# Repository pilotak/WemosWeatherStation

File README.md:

# Wemos weather station

An all-in-one ESP8266 based weather station. Hardware configuration is split into two parts due to easier maintenance in case of ESP8266 failure and fuse replacement (the board outside is protected against lighting). FW can easily be compiled by PlatformIO or Arduino IDE if necessary, otherwise can be downloaded in **Releases**.

Data are sent over MQTT where [Telegraf](https://www.influxdata.com/time-series-platform/telegraf/) is waiting to push data to [InfluxDB](https://www.influxdata.com/time-series-platform/influxdb/) and [Grafana](https://grafana.com/) tool to render charts.

**Main futures:**
- Easy configuration via [WiFiManager](https://github.com/tzapu/WiFiManager)
- WeMos based shield
- WH1080 mechanical components for rain, wind measurements and radiation shield
- MCP9808: high precision temperature sensor
- HTU21D or SHT31D: humidity sensor
- BMP280 or LPS35HW: pressure sensor
- Output data is via MQTT
- supports Arduino OTA, HTTP OTA and [NoFuss OTA](https://github.com/xoseperez/espurna)

*Note: on the board there can be only one humidity sensor, one pressure sensor and one temperature sensor in any combination, please see `platformio.ini`*

## Wemos-meteo shield
Based on my libraries:
- [WeatherMeters](https://github.com/pilotak/WeatherMeters)
- [MeteoFunctions](https://github.com/pilotak/MeteoFunctions)

### MQTT topics:
#### `name/status`
If online:
`sensors` key: binary map of sensors state (OK=1, failure=0)
```json
{
  "status": 1,
  "ip": "192.168.1.7",
  "rssi": -10,
  "sensors": 7,
  "fw_ver": "1.0.0"
}
```

otherwise:
```json
{
  "status": 0
}
```

#### `name/sensors`
If any of the value can't be calculated, it sends `NaN`
```json
{
  "humidity_rel": 79.84,
  "humidity_abs": 14.93,
  "pressure_rel": 1021.85,
  "pressure_abs": 967.55,
  "dew": 2.13,
  "humidex": 3.69,
  "heat": 3.97,
  "cloud": 390.13,
  "temp": [
    5.32,
    5.36,
    5.43
  ]
}
```

#### `name/upgrade`
As a data send link to `*.bin` upgrade package and it will reply in topic `name/upgrade/status`
(HTTP support only) *ie.: `http://somewebsite.com/upload/package.bin`*

#### `name/height`
As a data send new height and it will confirm in topic `name/height/new`

<table border="0">
 <tr>
    <td></td>
    <td></td>
 </tr>
</table>

## Weather board
Fits directly into radiation shield, just connect wind sensors, rain gauge bucket and you ready to measure. For future i have included extention connector for measuring sun light and UV index.

**_Update, I have created a sencond version of WeatherBoard with water-proof sensors SHT31D and LPS35HW but be carefull they are difficult to solder due to its size._**

<table border="0">
 <tr>
    <td></td>
    <td></td>
    <td></td>
 </tr>
 <tr>
    <td></td>
    <td></td>
    <td></td>
 </tr>
</table>

## Server configuration
Below you can find a `docker-compose.yaml` file for fast integration onto your server.
```yaml
version: "3.6"

services:
  mosquitto:
    container_name: mosquitto
    restart: always
    image: eclipse-mosquitto
    ports:
      - 1883:1883
    volumes:
      - ${DOCKER_PATH}/mosquitto/mosquitto.conf:/mosquitto/config/mosquitto.conf
      - ${DOCKER_PATH}/mosquitto/pwfile:/mosquitto/config/pwfile
      - ${DOCKER_PATH}/mosquitto/data:/mosquitto/data

  influxdb:
    container_name: influxdb
    restart: always
    image: influxdb:alpine
    environment:
      - INFLUXDB_REPORTING_DISABLED=true
      - INFLUXDB_DB=${INFLUX_DB}
      - INFLUXDB_ADMIN_USER=${INFLUX_ADMIN_USER}
      - INFLUXDB_ADMIN_PASSWORD=${INFLUX_ADMIN_PASSWORD}
      - INFLUXDB_USER=${INFLUX_USER}
      - INFLUXDB_USER_PASSWORD=${INFLUX_PASSWORD}
      - INFLUXDB_READ_USER=${INFLUX_READ_USER}
      - INFLUXDB_READ_USER_PASSWORD=${INFLUX_READ_PASSWORD}
      - INFLUXDB_WRITE_USER=${INFLUX_WRITE_USER}
      - INFLUXDB_WRITE_USER_PASSWORD=${INFLUX_WRITE_PASSWORD}
      - INFLUXDB_HTTP_AUTH_ENABLED=true
    volumes:
      - ${DOCKER_PATH}/influxdb:/var/lib/influxdb
    ports:
      - 8086:8086

  grafana:
    container_name: grafana
    restart: always
    image: grafana/grafana
    depends_on:
      - influxdb
    environment:
      - GF_ANALYTICS_REPORTING_ENABLED=false
      - GF_ANALYTICS_CHECK_FOR_UPDATES=false
      - GF_SECURITY_DISABLE_GRAVATAR=true
      - GF_SNAPSHOTS_EXTERNAL_ENABLED=false
      - GF_AUTH_ANONYMOUS_ENABLED=true
      - GF_AUTH_ANONYMOUS_ORG_NAME=${INFLUX_DB}
      - GF_AUTH_ANONYMOUS_ORG_ROLE=Viewer
      - GF_AUTH_DISABLE_SIGNOUT_MENU=true
      - GF_AUTH_BASIC_ENABLED=false
      - GF_SERVER_ROOT_URL=https://meteo.${MY_DOMAIN}
    volumes:
      - ${DOCKER_PATH}/grafana:/var/lib/grafana
    ports:
      - 3000:3000

  telegraf_meteo:
    container_name: telegraf_meteo
    restart: always
    image: telegraf:alpine
    depends_on:
      - influxdb
      - mosquitto
    volumes:
      - ${DOCKER_PATH}/telegraf/meteo.conf:/etc/telegraf/telegraf.conf:ro

```

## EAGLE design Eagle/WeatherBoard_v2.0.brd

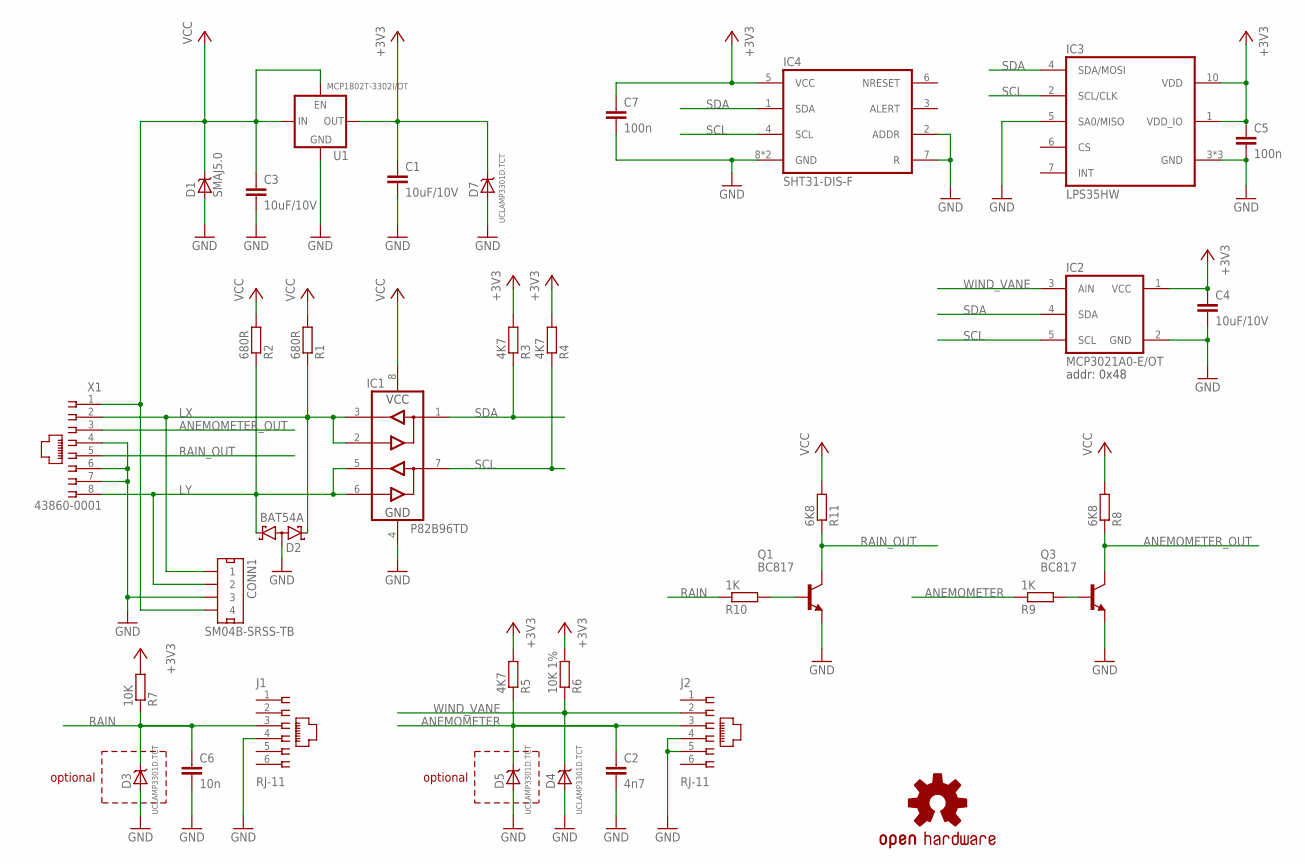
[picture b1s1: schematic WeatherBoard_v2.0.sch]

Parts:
C1, C3, C4: 10uF/10V; C0805
C2: 4n7; C0805
C5, C7: 100n; C0805
C6: 10n; C0805
CONN1: SM04B-SRSS-TB; JST-SRSS-4-T
D1: SMAJ5.0; DO214AC
D2: BAT54A; SOT23
D3, D4, D5, D7: UCLAMP3301D.TCT; SOD323
IC1: P82B96TD; SO08
IC2: MCP3021A0-E/OT; SOT23-5
IC3: LPS35HW; CCLGA10L
IC4: SHT31-DIS-F; DFN8
J1, J2: RJ-11; 615006138421
LOGO1: OSHW-LOGOM-COPPER; OSHW-LOGO-M_COPPER
Q1, Q3: BC817; SOT23-BEC
R1, R2: 680R; R0805
R3, R4, R5: 4K7; R0805
R6: 10K 1%; R0805
R7: 10K; R0805
R8, R11: 6K8; R0805
R9, R10: 1K; R0805
U1: MCP1802T-3302I/OT; SOT23-5
X1: 43860-0001; MX-43860-0001

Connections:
+3V3: C1.1, C4.1, C5.1, C7.1, D7.C, IC2.1 (VCC), IC3.1 (VDD_IO), IC3.10 (VDD), IC4.5 (VCC), R3.2, R4.2, R5.2, R6.2, R7.2, U1.5 (VOUT)
ANEMOMETER: C2.1, D5.C, J2.3, R5.1, R9.1
ANEMOMETER_OUT: Q3.C, R8.1, X1.3
GND: C1.2, C2.2, C3.2, C4.2, C5.2, C6.2, C7.2, CONN1.3, D1.A, D2.3 (AA), D3.A, D4.A, D5.A, D7.A, IC1.4 (GND), IC2.2 (GND), IC3.3 (GND), IC3.5 (SA0/MISO), IC3.8 (GND), IC3.9 (GND), IC4.2 (ADDR), IC4.7 (R), IC4.8 (GND), IC4.PAD (GND), J1.4, J2.4, J2.5, Q1.E, Q3.E, U1.2 (GND), X1.4, X1.6, X1.7
LX: CONN1.1, D2.2 (K2), IC1.2 (RX), IC1.3 (TX), R1.1, X1.2
LY: CONN1.2, D2.1 (K1), IC1.5 (TY), IC1.6 (RY), R2.1, X1.8
unnamed: Q3.B, R9.2
unnamed: Q1.B, R10.2
RAIN: C6.1, D3.C, J1.3, R7.1, R10.1
RAIN_OUT: Q1.C, R11.1, X1.5
SCL: IC1.7 (SY), IC2.5 (SCL), IC3.2 (SCL/CLK), IC4.4 (SCL), R4.1
SDA: IC1.1 (SX), IC2.4 (SDA), IC3.4 (SDA/MOSI), IC4.1 (SDA), R3.1
VCC: C3.1, CONN1.4, D1.C, IC1.8 (VCC), R1.2, R2.2, R8.2, R11.2, U1.1 (VIN), U1.3 (EN), X1.1
WIND_VANE: D4.C, IC2.3 (AIN), J2.2, R6.1

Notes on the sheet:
addr: 0x48
optional

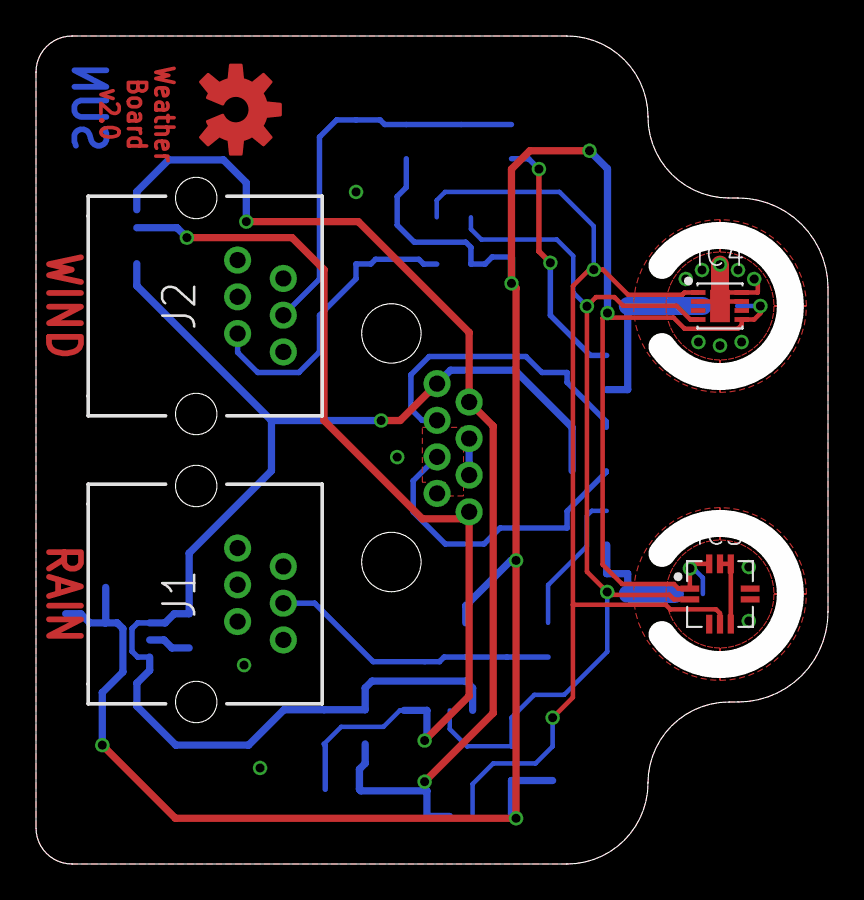
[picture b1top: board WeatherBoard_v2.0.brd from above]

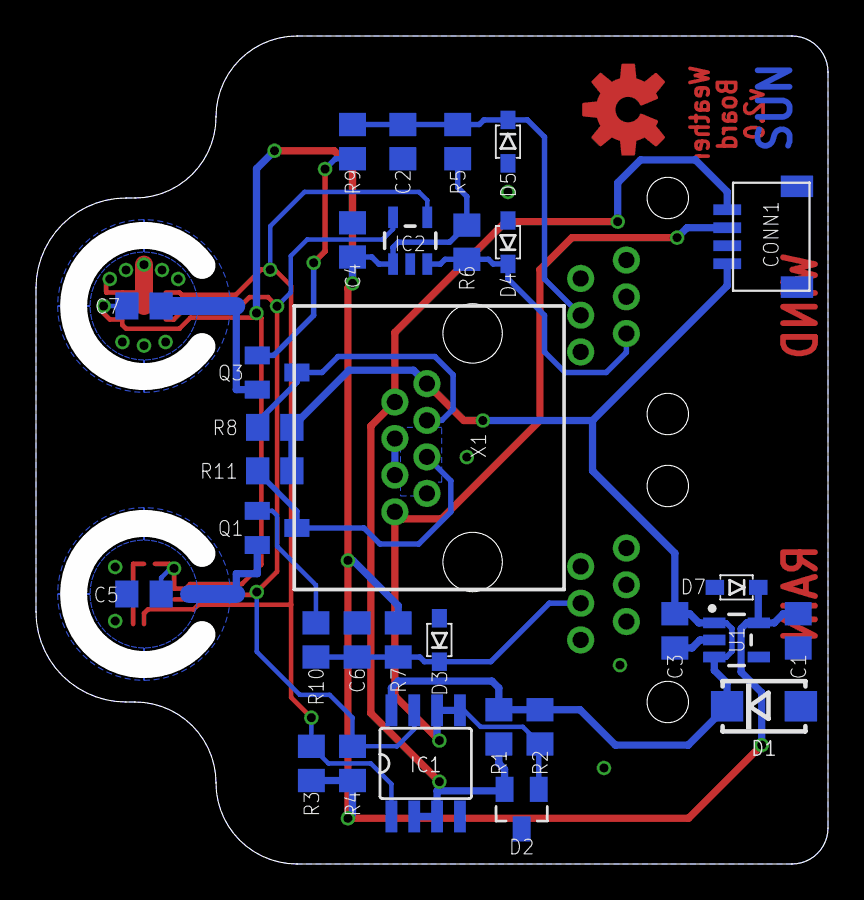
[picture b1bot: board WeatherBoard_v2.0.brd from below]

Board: 2 copper layers, 44.0 x 46.0 mm, 36 parts (31 on the bottom side), 14 nets.

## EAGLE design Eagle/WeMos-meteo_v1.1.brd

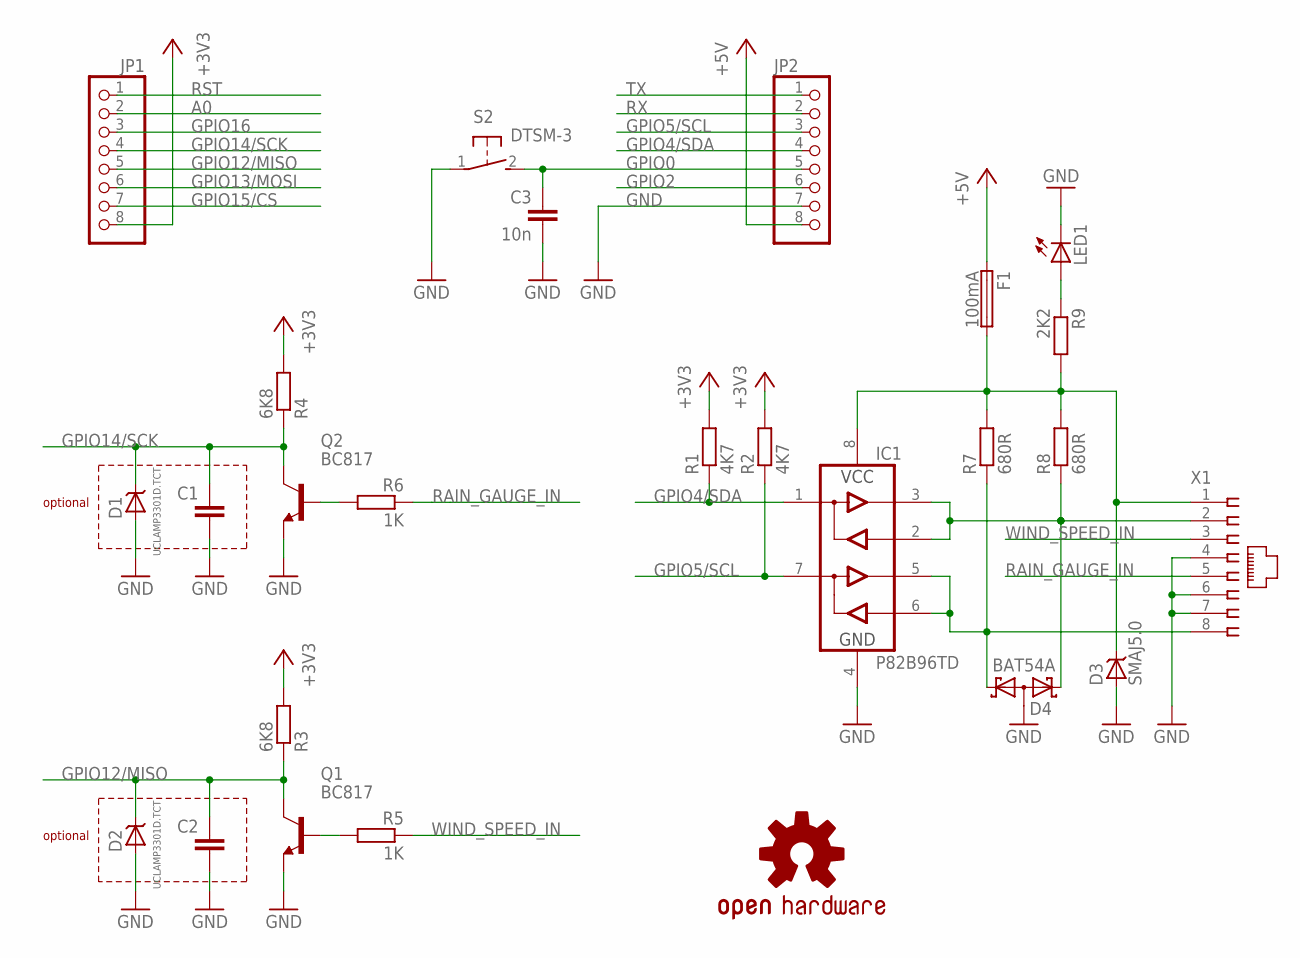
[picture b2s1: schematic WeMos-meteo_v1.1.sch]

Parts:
C1, C2: C-EUC0805; C0805
C3: 10n; C0805
D1, D2: UCLAMP3301D.TCT; SOD323
D3: SMAJ5.0; DO214AC
D4: BAT54A; SOT23
F1: 100mA; 19560
IC1: P82B96TD; SO08
JP1, JP2: PINHD-1X08_2.54-S; 1X08-S
LED1: LED0805
LOGO1: OSHW-LOGOMINI; OSHW-LOGO-MINI
Q1, Q2: BC817; SOT23-BEC
R1, R2: 4K7; R0805
R3, R4: 6K8; R0805
R5, R6: 1K; R0805
R7, R8: 680R; R0805
R9: 2K2; R0805
S2: DTSM-3
X1: RJ-45; 95501

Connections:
+3V3: JP1.8, R1.2, R2.2, R3.2, R4.2
+5V: F1.1, JP2.8
A0: JP1.2
GND: C1.2, C2.2, C3.2, D1.A, D2.A, D3.A, D4.3 (AA), IC1.4 (GND), JP2.7, LED1.C, Q1.E, Q2.E, S2.1, X1.4, X1.6, X1.7
GPIO0: C3.1, JP2.5, S2.2
GPIO2: JP2.6
GPIO4/SDA: IC1.1 (SX), JP2.4, R1.1
GPIO5/SCL: IC1.7 (SY), JP2.3, R2.1
GPIO12/MISO: C2.1, D2.C, JP1.5, Q1.C, R3.1
GPIO13/MOSI: JP1.6
GPIO14/SCK: C1.1, D1.C, JP1.4, Q2.C, R4.1
GPIO15/CS: JP1.7
GPIO16: JP1.3
unnamed: D4.2 (K2), IC1.2 (RX), IC1.3 (TX), R8.1, X1.2
unnamed: D4.1 (K1), IC1.5 (TY), IC1.6 (RY), R7.1, X1.8
unnamed: Q1.B, R5.2
unnamed: Q2.B, R6.2
unnamed: LED1.A, R9.1
RAIN_GAUGE_IN: R6.1, X1.5
RST: JP1.1
RX: JP2.2
TX: JP2.1
VCC: D3.C, F1.2, IC1.8 (VCC), R7.2, R8.2, R9.2, X1.1
WIND_SPEED_IN: R5.1, X1.3

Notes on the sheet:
optional

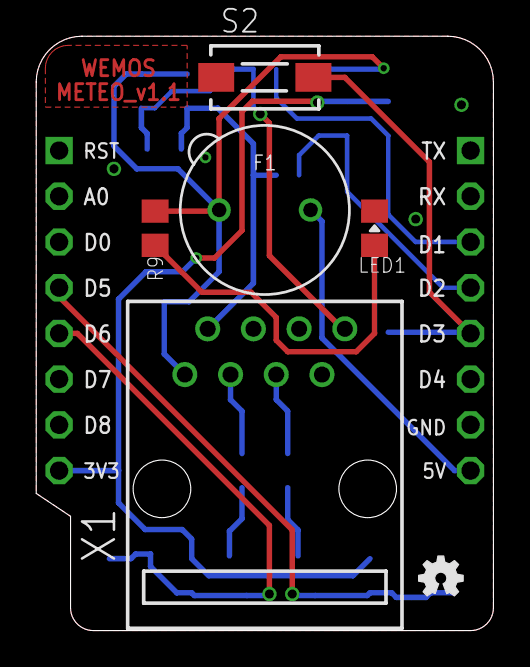
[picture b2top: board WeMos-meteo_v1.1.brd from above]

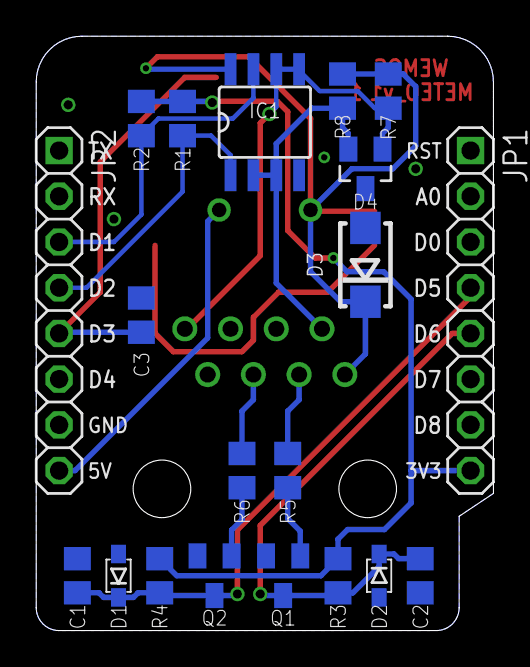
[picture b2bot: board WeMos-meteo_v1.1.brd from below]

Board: 2 copper layers, 25.4 x 33.0 mm, 26 parts (20 on the bottom side), 16 nets.

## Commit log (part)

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2018-09-15 init
2018-09-25 badge
2018-09-27 meteo functions added
2018-09-27 interrupt stop on OTA + enable timer WM
2018-10-14 mqtt IP check
2018-10-14 BME address fix
2018-10-17 check if sensors are available
2018-10-17 check for NAN and empty JSON
2018-10-17 http ota
2018-10-25 height_above_sea to WiFiManager + fixes
2018-10-26 button dep fix
2018-10-26 height above sea configurable over MQTT
2018-10-31 status as json
2018-12-09 sensor counter fix + SAMPLES macro rename
2018-12-09 http update rework + mqtt confirmation update
2018-12-09 new dir filtering
2018-12-13 dependencies update
2019-01-01 src files
2019-01-01 readme + licence update
    [ci skip]
2019-01-01 image align
2019-01-01 update
    [ci skip]
2019-01-01 borders
2019-01-01 borders update
2019-01-13 specify sensors at build
2019-01-13 dependency fix
2019-02-10 set default I2C speed
2019-05-01 async wifi manager + config on demand
2019-05-01 bmp280 settings compile fix
2019-05-01 check is config exists + custom html
2019-05-01 WifiManager parse int numbers
2019-05-01 temp nestedArray fix
2019-06-14 prepare for different sensors
2019-06-23 support different sensors
2019-06-23 send fw_ver
2019-06-23 update README
    [ci skip]
2019-06-24 bug fix
2019-07-01 above sea Manager fix
2019-07-01 readme update
2019-07-01 eagle files for V2.0
2019-07-14 create config if doesn't exists + PIO 4.0 + delay after OTA
2019-07-16 allow redirects in ota
2020-12-21 GithubCI
2020-12-21 add dependency
2020-12-21 restructure for CI
2021-05-12 V2 with BPM280
2021-05-13 bump version
2021-05-25 split sensor code + LittleFS
2021-05-25 debug update
2021-08-05 BMP compile fix

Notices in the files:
parts and their libraries:
SparkFun-Aesthetics: Licensing: Creative Commons ShareAlike 4.0 International - https://creativecommons.org/licenses/by-sa/4.0
